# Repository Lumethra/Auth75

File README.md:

# Auth 75

## What is this? 

This is a 75% keyboard with a fingerprint sensor. What? A fingerprint sensor in a keyboard? Yes, you've heard it right! This keyboard includes a working fingerprint sensor. But how does it work? Aren't fingerprint sensors tied to motherboards? Continue reading, to get an answer to this question. 

### Features: 
  - Keycool84 layout (modified)
  - Raspberry Pi Pico 2W
    - ZMK (not tested)
    - LiPo battery
    - Battery charger
  - Rotary Encoder Switch (EC11)
  - USB Hub (SL2.1)
    - 1 USB-C upstream
    - 2 USB-C downstreams
    - 1 notched FPC-connector (fingerprint sensor)
    - 1 USB-C to connect to the Pico

---

## Why? 

I always wanted a good keyboard with a working fingerprint sensor, because my password is always too long and I am used to the one on my laptop. Why not just use the one on my laptop? Because I want to close my laptop lid while using a monitor. The second reason is that the one on my laptop doesnt work on Linux, so I wanted to make compatible with my main OS. 

---

## How? 

I did some research and found out that the Framework 13 Fingerprint Reader isnt tied to their motherboard, unlike Lenovo or Dell. I also found a [Framework-Community-Post](https://community.frame.work/t/framework-fingerprint-scanner-for-a-desktop-pc/29845), where the people managed to use the sensor via USB-C. They also found out that the D+ and D- pins are inverted. A huge thank you to these guys. After buying the sensor and testing its functionalty at home, I decided on using a USB-Hub to have the fingerprint reader and the keyboard MCU in on connector. Frameworks support also helped me out with the fingerprint sensor datasheet. And now I've got a 75% keyboard with a working fingerprint sensor. 

---

## Renders

| PCB with Components | 
| --- |
|  |
|  |

| PCB without Components |
| --- |
|  |
|  |

| Case |
| --- |
|  |
| Thank you Chroma for making this wonderful case |
| The case source files are [here](https://cad.onshape.com/documents/94c98908253eab7c65b6f4cc/w/cb3c129046b9b5460a1f53f5/e/8f22757c89f8236cf1eb1f99?renderMode=0&uiState=6a16d4e81bc895272aca484b) |

---

## PCB + Schematics

| Schematics |
| --- |
|  |

| PCB |
| --- |
|  |

---
<details>
  <summary>
    <h2>Zine</h2> 
  </summary>

| Zine |
| --- |
|  |

---
</details>

## BOM

| Part | Purpose | Cost | Quantity | Total Cost | LCSC/JLCPCB Number | Link |
| --- | --- | --- | --- | --- | --- | --- |
| PCB | connecting every component | ~ | 1 (5) | $22.60 | ~ | [JLCPCB](https://jlcpcb.com/) |
| Pico 2W | main MCU (handeling software) | ~$7 | 1 | $7 | C42394205 (JLCPCB) | [Raspberry Pi](https://www.raspberrypi.com/products/raspberry-pi-pico-2/) |
| Kailh Hotswap Sockets | holding the switches to the PCB without soldering | $0.1183 | 78 | ~$9 | C2803348 | [JLCPCB](https://jlcpcb.com/partdetail/C2803348) |
| Kailh (Cocoa) Switches | the switches you can press | $0 (comes with a Rainy75) | 78 | $0 (already owned) | ~ | ~ |
| Keycaps | goes onto the switches for better look and feel | $0 (3d printing ABS) | 78 | $0 (3d printed) | ~ | ~ |
| EC11 Rotary Encoder Switch | goes uii and click click | $2.22 | 1 | $2.22 | C370970 | [JLCPCB](https://jlcpcb.com/partdetail/C370970) / [Amazon](https://www.amazon.de/-/en/RUNCCI-YUN-Potentiometer-Automotive-Electronics-Multimedia/dp/B09SG3HF9N) |
| Fingerprint Reader Kit | recognize your finger | $29.00 | 1 | $29.00 | ~ | [Framework](https://frame.work/products/fingerprint-reader-kit?v=FRANTD0001) |
| KYOCERA AVX FPC Connector | connect the fingerprint sensor | $0.3775 | 1 | $0.3775 | C5464531 | [JLCPCB](https://jlcpcb.com/partdetail/C5464531) |
| USB-C connector | connect to laptop | $0.0740 | 4 | $0.296 | C2765186 | [JLCPCB](https://jlcpcb.com/partdetail/C2765186) |
| PCA9536DGKR | I2C GPIO expander (more GPIO pins, yeeee) | $1.2053 | 1 | $1.2053 | C2649389 | [JLCPCB](https://jlcpcb.com/partdetail/C2649389) |
| SL2.1s | USB Hub core component | $0.2258 | 1 | $0.2258 | C2684433 | [JLCPCB](https://jlcpcb.com/partdetail/C2684433) |
| MMBT3904 | letting the Pi control the LEDs on the sensor | $0.0095 | 3 | $0.0285 | C20526 | [JLCPCB](https://jlcpcb.com/partdetail/C20526) |
| SS8550 Y2 | implementing the sensor switch into the matrix | $0.0134 | 1 | $0.0134 | C8542 | [JLCPCB](https://jlcpcb.com/partdetail/C8542) |
| MCP73831T-2ACI/OT | battery charger | $0.7585 | 1 | $0.7585 | C424093 | [JLCPCB](https://jlcpcb.com/partdetail/C424093) |
| DW01A | battery protector | $0.0426 | 1 | $0.0426 | C351410 | [JLCPCB](https://jlcpcb.com/partdetail/C351410) |
| FS8205A | mosfet for protector | $0.0470 | 1 | $0.0470 | C2830320 | [JLCPCB](https://jlcpcb.com/partdetail/C2830320) |
| S2B-PH-SM4-TB | connector for battery | $0.2014 | 1 | $0.2014 | C295747 | [JLCPCB](https://jlcpcb.com/partdetail/C295747) |
| Resistors | prevent things go boom | ~$0.0016 | 19 | ~$0.0304 | C23186, C21190, C22775, C23162 | [C23186](https://jlcpcb.com/partdetail/C23186) / [C21190](https://jlcpcb.com/partdetail/C21190) / [C22775](https://jlcpcb.com/partdetail/C22775) / [C23162](https://jlcpcb.com/partdetail/C23162) |
| Diodes | prevent voltage from backflowing | $0.0117 | 82 | ~$0.9594 | C81598 | [JLCPCB](https://jlcpcb.com/partdetail/C81598) |
| Capacitors | smooth out the power | $0.0032 - $0.0110 | 14 | ~$0.0956 | C15849, C19666, C14663 | [C15849](https://jlcpcb.com/partdetail/C15849) / [C19666](https://jlcpcb.com/partdetail/C19666) / [C14663](https://jlcpcb.com/partdetail/C14663) |

> the prices can vary depending on the provider <br>
> you can find the JLCPCB parts on [LCSC](https://lcsc.com/) too (exept the PCB and the Pico) <br>
> note: u could solder a pico 2 on there instead, cause its physically the same

---

## Contribute

Want to make it better? Found some bugs? Feel free to open a PR (pull request) and lets make the project better. ^_^
> the libraries are all imported with [easyeda2kicad](https://github.com/uPesy/easyeda2kicad.py) and [kiswitch](https://github.com/kiswitch/kiswitch)

---

## Thank you

A huge thank you to all these guys helping me out with my project. <br>
[@eggsplats](https://github.com/geg-tech), [@Kai Pereira](https://github.com/KaiPereira), [@Aadit Bhambri](https://github.com/abinnovator), [@technical_.](https://github.com/techn1-cal) and [@Tanuki](https://github.com/TaniWanKenobi) for helping out on my way and inspiring me with their passion and projects. <br>
Another thank you to my sister (for **some** of the art), the Framework support (for the datasheet of the sensor), the guys in the [Framework-Community-Post](https://community.frame.work/t/framework-fingerprint-scanner-for-a-desktop-pc/29845) (for the functionality of the sensor), my [friend](https://github.com/Chroma165) (for the case and 3d model of the fingerprint sensor) and my [other friend](https://github.com/Leonhoch5) (for the emotional support)
> Thank you guys <3

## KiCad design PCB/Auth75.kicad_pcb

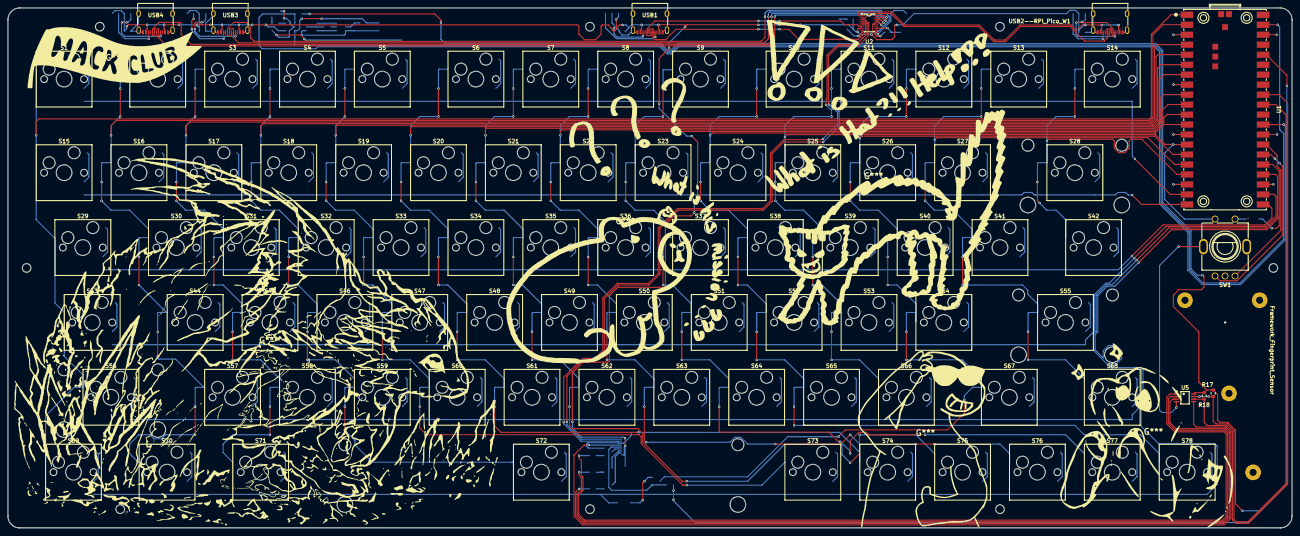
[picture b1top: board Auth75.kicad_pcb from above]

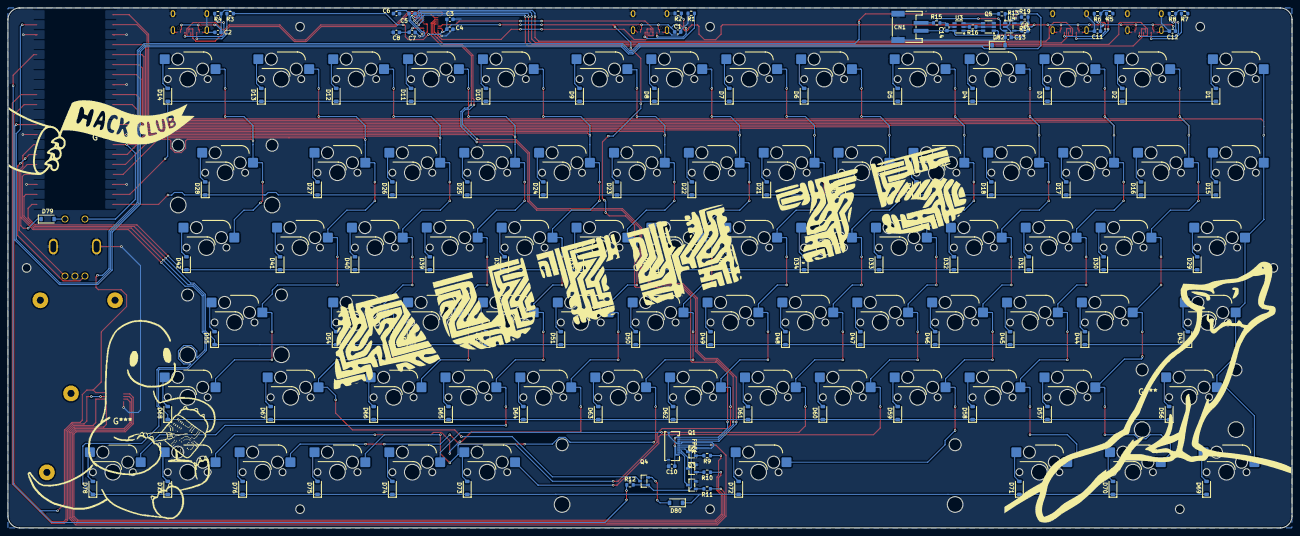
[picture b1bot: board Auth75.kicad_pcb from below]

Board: 2 copper layers, 326.7 x 132.3 mm, 210 parts (121 on the bottom side), 149 nets.

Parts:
C1, C2, C3, C5, C7, C10, C11, C12: 1uF; C_0603_1608Metric
C4, C6, C8, C14: 100nF; C_0603_1608Metric
C9, C13: 4.7uF; C_0603_1608Metric
CN1: S2B-PH-SM4-TB; CONN-SMD_P2.00_S2B-PH-SM4-TB-LF-SN
D1, D2, D3, D4, D5, D6, D7, D8, D9, D10, D11, D12, D13, D14, D15, D16, D17, D18, D19, D20, D21, D22, D23, D24, D25, D26, D27, D28, D29, D30, D31, D32, D33, D34, D35, D36, D37, D38, D39, D40, D41, D42, D43, D44, D45, D46, D47, D48, D49, D50, D51, D52, D53, D54, D55, D56, D57, D58, D59, D60, D61, D62, D63, D64, D65, D66, D67, D68, D69, D70, D71, D72, D73, D74, D75, D76, D77, D78, D79, D80, D82: D_SOD-123
FPC1: 046809610110846+; CONN-SMD_10P-P0.50_046809610110846
Framework_Fingerprint_Sensor: Untitled; Framework Fingerprint Sensor
Q1, Q2, Q3: MMBT3904-C20526; SOT-23-3_L2.9-W1.3-P1.90-LS2.4-BR
Q4: SS8550_C8542; SOT-23-3_L2.9-W1.3-P1.90-LS2.4-BR
Q5: FS8205A_C2830320; SOT-23-6_L2.9-W1.6-P0.95-LS2.8-BR
R1, R2, R12, R13: 5.1k; R_0603_1608Metric
R3, R4, R5, R6, R7, R8: 56k; R_0603_1608Metric
R9, R10, R11, R14, R16, R19: 1k; R_0603_1608Metric
R15: 100; R_0603_1608Metric
R17, R18: 4.7k; R_0603_1608Metric
S1, S2, S3, S4, S5, S6, S7, S8, S9, S10, S11, S12, S13, S14, S15, S16, S17, S18, S19, S20, S21, S22, S23, S24, S25, S26, S27, S28, S29, S30, S31, S32, S33, S34, S35, S36, S37, S38, S39, S40, S41, S42, S43, S44, S45, S46, S47, S48, S49, S50, S51, S52, S53, S54, S55, S56, S57, S58, S59, S60, S61, S62, S63, S64, S65, S66, S67, S68, S69, S70, S71, S72, S73, S74, S75, S76, S77, S78: SW_Hotswap_Kailh_MX
SW1: EC11E15244G1; SW-TH_EC11E15244G1
U1: RASPBERRY PI PICO 2W; COMM-SMD_L51.0-W21.0-P2.54_PICOW
U2: SL2.1S; SSOP-16_L4.6-W2.6-P0.53-LS4.0-BL
U3: DW01A_C351410; SOT-23-6_L2.9-W1.6-P0.95-LS2.8-BL
U4: MCP73831T-2ACI/OT; SOT-23-5_L3.0-W1.7-P0.95-LS2.8-BL
U5: PCA9536DGKR; VSSOP-8_L3.0-W3.0-P0.65-LS4.9-BL
USB1, USB2--RPI_Pico_W1, USB3, USB4: TYPE-C 16PIN 2MD; USB-C-SMD_TYPE-C-6PIN-2MD-073

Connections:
+3.3V: R12.1, R13.1, R17.2, R18.2, U1.36 (3V3(OUT)), U5.8 (VCC)
+5V: C1.1, C2.1, C3.1, C4.1, C9.1, C10.1, C11.1, C12.1, FPC1.1, FPC1.10, R3.1, R4.1, R5.1, R6.1, R7.1, R8.1, U2.7 (VDD5), U4.4 (VDD), USB1.2 (VBUS), USB1.11 (VBUS), USB2--RPI_Pico_W1.2 (VBUS), USB2--RPI_Pico_W1.11 (VBUS), USB3.2 (VBUS), USB3.11 (VBUS), USB4.2 (VBUS), USB4.11 (VBUS)
/D1/D2: Q5.2 (D1/D2), Q5.5 (D1/D2), R16.1
/DN: U2.5 (UDM), USB1.5 (DN2), USB1.7 (DN1)
/DN1: FPC1.2, U2.3 (DM1)
/DN2: U2.1 (DM2), USB2--RPI_Pico_W1.5 (DN2), USB2--RPI_Pico_W1.7 (DN1)
/DN3: U2.15 (DM3), USB3.5 (DN2), USB3.7 (DN1)
/DN4: U2.13 (DM4), USB4.5 (DN2), USB4.7 (DN1)
/DP: U2.6 (UDP), USB1.6 (DP1), USB1.8 (DP2)
/DP1: FPC1.3, U2.4 (DP1)
/DP2: U2.2 (DP2), USB2--RPI_Pico_W1.6 (DP1), USB2--RPI_Pico_W1.8 (DP2)
/DP3: U2.16 (DP3), USB3.6 (DP1), USB3.8 (DP2)
/DP4: U2.14 (DP4), USB4.6 (DP1), USB4.8 (DP2)
BATT+: C13.1, CN1.1, D82.2 (A), R15.2, U4.3 (VBAT)
BATT-: C14.1, CN1.2, Q5.1 (S1), U3.6 (GND)
Column 1: S1.1, S15.1, S29.1, S43.1, S56.1, S69.1, U1.1 (GP0_SPI0RX_I2C0SDA_UART0TX)
Column 2: S2.1, S16.1, S30.1, S44.1, S57.1, S70.1, U1.2 (GP1_SPI0CSn_I2C0SCL_UART0RX)
Column 3: S3.1, S17.1, S31.1, S45.1, S58.1, S71.1, U1.4 (GP2_SPI0SCK_I2C1SDA)
Column 4: S4.1, S18.1, S32.1, S46.1, S59.1, S72.1, U1.5 (GP3_SPI0TX_I2C1SCL)
Column 5: S5.1, S19.1, S33.1, S47.1, S60.1, S73.1, U1.6 (GP4_SPI0RX_I2C0SDA_UART1TX)
Column 6: S6.1, S20.1, S34.1, S48.1, S61.1, S74.1, U1.7 (GP5_SPI0CSn_I2C0SCL_UART1RX)
Column 7: S7.1, S21.1, S35.1, S49.1, S62.1, S75.1, U1.9 (GP6_SPI0SCK_I2C1SDA)
Column 8: S8.1, S22.1, S36.1, S50.1, S63.1, S76.1, U1.10 (GP7_SPI0TX_I2C1SCL)
Column 9: S9.1, S23.1, S37.1, S51.1, S64.1, S77.1, U1.11 (GP8_SPI1RX_I2C0SDA_UART1TX)
Column 10: S10.1, S24.1, S38.1, S52.1, S65.1, S78.1, U1.12 (GP9_SPI1CSn_I2C0SCL_UART1RX)
Column 11: S11.1, S25.1, S39.1, S53.1, S66.1, SW1.D, U1.14 (GP10_SPI1SCK_I2C1SDA)
Column 12: Q4.3 (C), S12.1, S26.1, S40.1, S54.1, S67.1, U1.15 (GP11_SPI1TX_I2C1SCL)
Column 13: S13.1, S27.1, S41.1, S55.1, S68.1, U1.16 (GP12_SPI1RX_I2C0SDA_UART0TX)
Column 14: S14.1, S28.1, S42.1, U1.17 (GP13_SPI1CSn_I2C0SCL_UART0RX)
Fprint LED Green MCU: R10.1, U5.2 (P1)
Fprint LED Red MCU: R11.1, U5.3 (P2)
Fprint LED White MCU: R9.1, U5.1 (P0)
Fprint Switch: FPC1.6, Q4.1 (B), R12.2
Fprint Switch Row: D80.2 (A), Q4.2 (E)
Fprint Touch: FPC1.5, U5.5 (P3)
GND: C1.2, C2.2, C3.2, C4.2, C5.2, C6.2, C7.2, C8.2, C9.2, C10.2, C11.2, C12.2, C13.2, CN1.3, CN1.4, FPC1.4, FPC1.11, FPC1.12, Q1.2 (E), Q2.2 (E), Q3.2 (E), Q5.3 (S2), R1.2, R2.2, R19.1, SW1.6, SW1.7, SW1.C, U1.3 (GND), U1.8 (GND), U1.13 (GND), U1.18 (GND), U1.23 (GND), U1.28 (GND), U1.38 (GND), U2.8 (VSS), U2.12 (XIN), U4.2 (VSS), U5.4 (GND), USB1.1 (GND), USB1.12 (GND), USB1.13 (SHELL), USB1.14 (SHELL), USB2--RPI_Pico_W1.1 (GND), USB2--RPI_Pico_W1.12 (GND), USB2--RPI_Pico_W1.13 (SHELL), USB2--RPI_Pico_W1.14 (SHELL), USB3.1 (GND), USB3.12 (GND), USB3.13 (SHELL), USB3.14 (SHELL), USB4.1 (GND), USB4.12 (GND), USB4.13 (SHELL), USB4.14 (SHELL)
K_O: D79.2 (A), SW1.E
Knob_A: SW1.A, U1.26 (GP20_I2C0SDA)
Knob_B: SW1.B, U1.27 (GP21_I2C0SCL)
LED Green: FPC1.8, Q2.3 (C)
LED Red: FPC1.9, Q3.3 (C)
LED White: FPC1.7, Q1.3 (C)
unnamed: D1.2 (A), S1.2
unnamed: D2.2 (A), S2.2
unnamed: D3.2 (A), S3.2
unnamed: D4.2 (A), S4.2
unnamed: D5.2 (A), S5.2
unnamed: D6.2 (A), S6.2
unnamed: D7.2 (A), S7.2
unnamed: D8.2 (A), S8.2
unnamed: D9.2 (A), S9.2
unnamed: D10.2 (A), S10.2
unnamed: D11.2 (A), S11.2
unnamed: D12.2 (A), S12.2
unnamed: D13.2 (A), S13.2
unnamed: D14.2 (A), S14.2
unnamed: D15.2 (A), S15.2
unnamed: D16.2 (A), S16.2
unnamed: D17.2 (A), S17.2
unnamed: D18.2 (A), S18.2
unnamed: D19.2 (A), S19.2
unnamed: D20.2 (A), S20.2
unnamed: D21.2 (A), S21.2
unnamed: D22.2 (A), S22.2
unnamed: D23.2 (A), S23.2
unnamed: D24.2 (A), S24.2
unnamed: D25.2 (A), S25.2
unnamed: D26.2 (A), S26.2
unnamed: D27.2 (A), S27.2
unnamed: D28.2 (A), S28.2
unnamed: D29.2 (A), S29.2
unnamed: D30.2 (A), S30.2
unnamed: D31.2 (A), S31.2
unnamed: D32.2 (A), S32.2
unnamed: D33.2 (A), S33.2
unnamed: D34.2 (A), S34.2
unnamed: D35.2 (A), S35.2
unnamed: D36.2 (A), S36.2
unnamed: D37.2 (A), S37.2
unnamed: D38.2 (A), S38.2
unnamed: D39.2 (A), S39.2
unnamed: D40.2 (A), S40.2
unnamed: D41.2 (A), S41.2
unnamed: D42.2 (A), S42.2
unnamed: D43.2 (A), S43.2
unnamed: D44.2 (A), S44.2
unnamed: D45.2 (A), S45.2
unnamed: D46.2 (A), S46.2
unnamed: D47.2 (A), S47.2
unnamed: D48.2 (A), S48.2
unnamed: D49.2 (A), S49.2
unnamed: D50.2 (A), S50.2
unnamed: D51.2 (A), S51.2
unnamed: D52.2 (A), S52.2
unnamed: D53.2 (A), S53.2
unnamed: D54.2 (A), S54.2
unnamed: D55.2 (A), S55.2
unnamed: D56.2 (A), S56.2
unnamed: D57.2 (A), S57.2
unnamed: D58.2 (A), S58.2
unnamed: D59.2 (A), S59.2
unnamed: D60.2 (A), S60.2
unnamed: D61.2 (A), S61.2
unnamed: D62.2 (A), S62.2
unnamed: D63.2 (A), S63.2
unnamed: D64.2 (A), S64.2
unnamed: D65.2 (A), S65.2
unnamed: D66.2 (A), S66.2
unnamed: D67.2 (A), S67.2
unnamed: D68.2 (A), S68.2
unnamed: D69.2 (A), S69.2
unnamed: D70.2 (A), S70.2
unnamed: D71.2 (A), S71.2
unnamed: D72.2 (A), S72.2
unnamed: D73.2 (A), S73.2
unnamed: D74.2 (A), S74.2
unnamed: D75.2 (A), S75.2
unnamed: D76.2 (A), S76.2
unnamed: D77.2 (A), S77.2
unnamed: D78.2 (A), S78.2
unnamed: D82.1 (K), U1.39 (VSYS)
unnamed: Q1.1 (B), R9.2
unnamed: Q2.1 (B), R10.2
unnamed: Q3.1 (B), R11.2
unnamed: Q5.6 (G1), U3.1 (OD)
unnamed: Q5.4 (G2), U3.3 (OC)
unnamed: R14.1, R19.2
unnamed: C7.1, C8.1, U2.10 (VDD18)
unnamed: C5.1, C6.1, U2.9 (VDD33)
unnamed: C14.2, R15.1, U3.5 (VCC)
unnamed: R16.2, U3.2 (VM)
unnamed: R14.2, U4.5 (PROG)
unnamed: R1.1, USB1.4 (CC1)
unnamed: R2.1, USB1.10 (CC2)
unnamed: R4.2, USB2--RPI_Pico_W1.4 (CC1)
unnamed: R3.2, USB2--RPI_Pico_W1.10 (CC2)
unnamed: R6.2, USB3.4 (CC1)
unnamed: R5.2, USB3.10 (CC2)
unnamed: R8.2, USB4.4 (CC1)
unnamed: R7.2, USB4.10 (CC2)
PCA9536DGKR SCL: R18.1, U1.32 (GP27_ADC1_I2C1SCL), U5.6 (SCL)
PCA9536DGKR SDA: R17.1, U1.31 (GP26_ADC0_I2C1SDA), U5.7 (SDA)
Row 1: D1.1 (K), D2.1 (K), D3.1 (K), D4.1 (K), D5.1 (K), D6.1 (K), D7.1 (K), D8.1 (K), D9.1 (K), D10.1 (K), D11.1 (K), D12.1 (K), D13.1 (K), D14.1 (K), U1.19 (GP14_SPI1SCK_I2C1SDA)
Row 2: D15.1 (K), D16.1 (K), D17.1 (K), D18.1 (K), D19.1 (K), D20.1 (K), D21.1 (K), D22.1 (K), D23.1 (K), D24.1 (K), D25.1 (K), D26.1 (K), D27.1 (K), D28.1 (K), U1.20 (GP15_SPI1TX_I2C1SCL)
Row 3: D29.1 (K), D30.1 (K), D31.1 (K), D32.1 (K), D33.1 (K), D34.1 (K), D35.1 (K), D36.1 (K), D37.1 (K), D38.1 (K), D39.1 (K), D40.1 (K), D41.1 (K), D42.1 (K), U1.21 (GP16_SPI0RX_UART0RX)
Row 4: D43.1 (K), D44.1 (K), D45.1 (K), D46.1 (K), D47.1 (K), D48.1 (K), D49.1 (K), D50.1 (K), D51.1 (K), D52.1 (K), D53.1 (K), D54.1 (K), D55.1 (K), U1.22 (GP17_SPI0CSn_UART0TX)
Row 5: D56.1 (K), D57.1 (K), D58.1 (K), D59.1 (K), D60.1 (K), D61.1 (K), D62.1 (K), D63.1 (K), D64.1 (K), D65.1 (K), D66.1 (K), D67.1 (K), D68.1 (K), U1.24 (GP18_SPI0SCK_I2C1SDA)
Row 6: D69.1 (K), D70.1 (K), D71.1 (K), D72.1 (K), D73.1 (K), D74.1 (K), D75.1 (K), D76.1 (K), D77.1 (K), D78.1 (K), D79.1 (K), D80.1 (K), U1.25 (GP19_SPI0TX_I2C1SCL)
STAT: R13.2, U1.29 (GP22), U4.1 (STAT)

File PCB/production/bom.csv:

Designator,Footprint,Quantity,Value,LCSC Part #
"C1, C10, C11, C12, C2, C3, C5, C7",0603,8,1uF,C15849
"C13, C9",0603,2,4.7uF,C19666
"C14, C4, C6, C8",0603,4,100nF,C14663
CN1,CONN-SMD_P2.00_S2B-PH-SM4-TB-LF-SN,1,S2B-PH-SM4-TB,C295747
"D1, D10, D11, D12, D13, D14, D15, D16, D17, D18, D19, D2, D20, D21, D22, D23, D24, D25, D26, D27, D28, D29, D3, D30, D31, D32, D33, D34, D35, D36, D37, D38, D39, D4, D40, D41, D42, D43, D44, D45, D46, D47, D48, D49, D5, D50, D51, D52, D53, D54, D55, D56, D57, D58, D59, D6, D60, D61, D62, D63, D64, D65, D66, D67, D68, D69, D7, D70, D71, D72, D73, D74, D75, D76, D77, D78, D79, D8, D80, D9",D_SOD-123,80,~,C81598
D81,0603,1,LED,C2286
D82,D_SOD-123,1,~,C169540
FPC1,CONN-SMD_10P-P0.50_046809610110846,1,046809610110846+,C5464531
"Q1, Q2, Q3",SOT-23-3_L2.9-W1.6-P1.90-LS2.8-BR,3,MMBT3904LT1G,C81464
Q4,SOT-23-3_L2.9-W1.3-P1.90-LS2.4-BR,1,MMBT3906LT1G,C53444
Q5,SOT-23-6_L2.9-W1.6-P0.95-LS2.8-BR,1,FS8205A_C2830320,C2830320
"R1, R2, R3, R4, R5, R6, R7, R8",0603,8,5.1k,C23186
"R10, R11, R16, R9",0603,4,1k,C21190
R12,0603,1,10k,C25804
R13,0603,1,470,C23179
R14,0603,1,2k,C22975
R15,0603,1,100,C22775
"R17, R18",0603,2,4.7k,C23162
"S1, S10, S11, S12, S13, S14, S15, S16, S17, S18, S19, S2, S20, S21, S22, S23, S24, S25, S26, S27, S3, S30, S31, S32, S33, S34, S35, S36, S37, S38, S39, S4, S40, S41, S44, S45, S46, S47, S48, S49, S5, S50, S51, S52, S53, S54, S57, S58, S59, S6, S60, S61, S62, S63, S64, S65, S66, S68, S7, S73, S74, S75, S76, S77, S78, S8, S9",SW_Hotswap_Kailh_MX_1.00u,67,~,C2803348
S28,SW_Hotswap_Kailh_MX_2.00u,1,~,C2803348
"S29, S42",SW_Hotswap_Kailh_MX_1.50u,2,~,C2803348
"S43, S67",SW_Hotswap_Kailh_MX_1.75u,2,~,C2803348
"S55, S56",SW_Hotswap_Kailh_MX_2.25u,2,~,C2803348
"S69, S70, S71",SW_Hotswap_Kailh_MX_1.25u,3,~,C2803348
S72,SW_Hotswap_Kailh_MX_6.25u,1,~,C2803348
U1,COMM-SMD_L51.0-W21.0-P2.54_PICOW,1,RASPBERRY PI PICO 2W,C42394205
U2,SSOP-16_L4.6-W2.6-P0.53-LS4.0-BL,1,SL2.1S,C2684433
U3,SOT-23-6_L2.9-W1.6-P0.95-LS2.8-BL,1,DW01A_C351410,C351410
U4,SOT-23-5_L3.0-W1.7-P0.95-LS2.8-BL,1,MCP73831T-2ACI/OT,C424093
U5,VSSOP-8_L3.0-W3.0-P0.65-LS4.9-BL,1,PCA9536DGKR,C2649389
"USB1, USB2--RPI_PICO_W1, USB3, USB4",USB-C-SMD_TYPE-C-6PIN-2MD-073,4,TYPE-C 16PIN 2MD,C2765186

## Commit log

2026-05-17 adding and improving lib and adding CAD
2026-05-17 uhh sth i dunno what, but savin
2026-05-17 where the heck did my last commits go
2026-05-21 adding battery charger
2026-05-23 Wrap up project and adding silkscreen
2026-05-24 adding screenshots
2026-05-24 adding images
2026-05-25 Finishing BOM
2026-05-25 finishing readme
    missing case design, but whatever
2026-05-25 Enhance thank you section in README
    Expanded the gratitude section to include additional appreciation for the contributors' passion and projects.
2026-05-25 aaaaa
2026-05-25 adding the compiled firmware as zip
2026-05-25 new firmware with encoder
2026-05-26 add firmware readme, that souce code is in another repo
2026-05-26 dont know what the heck
2026-05-26 linking every part specifically
2026-05-26 cleaning up, i forgot
2026-05-26 hope this counts as links
2026-05-26 adding name
2026-05-27 yeeeeeeeeeeee
2026-05-27 Case.png
2026-05-27 Case
2026-05-28 rename Zine to zine
2026-06-07 making a cheaper version
2026-06-12 56k resis for pull up
